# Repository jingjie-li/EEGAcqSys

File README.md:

# EEGAcqSys
A EEG acquisition and online processing system based on ADS1299 and TI DSP

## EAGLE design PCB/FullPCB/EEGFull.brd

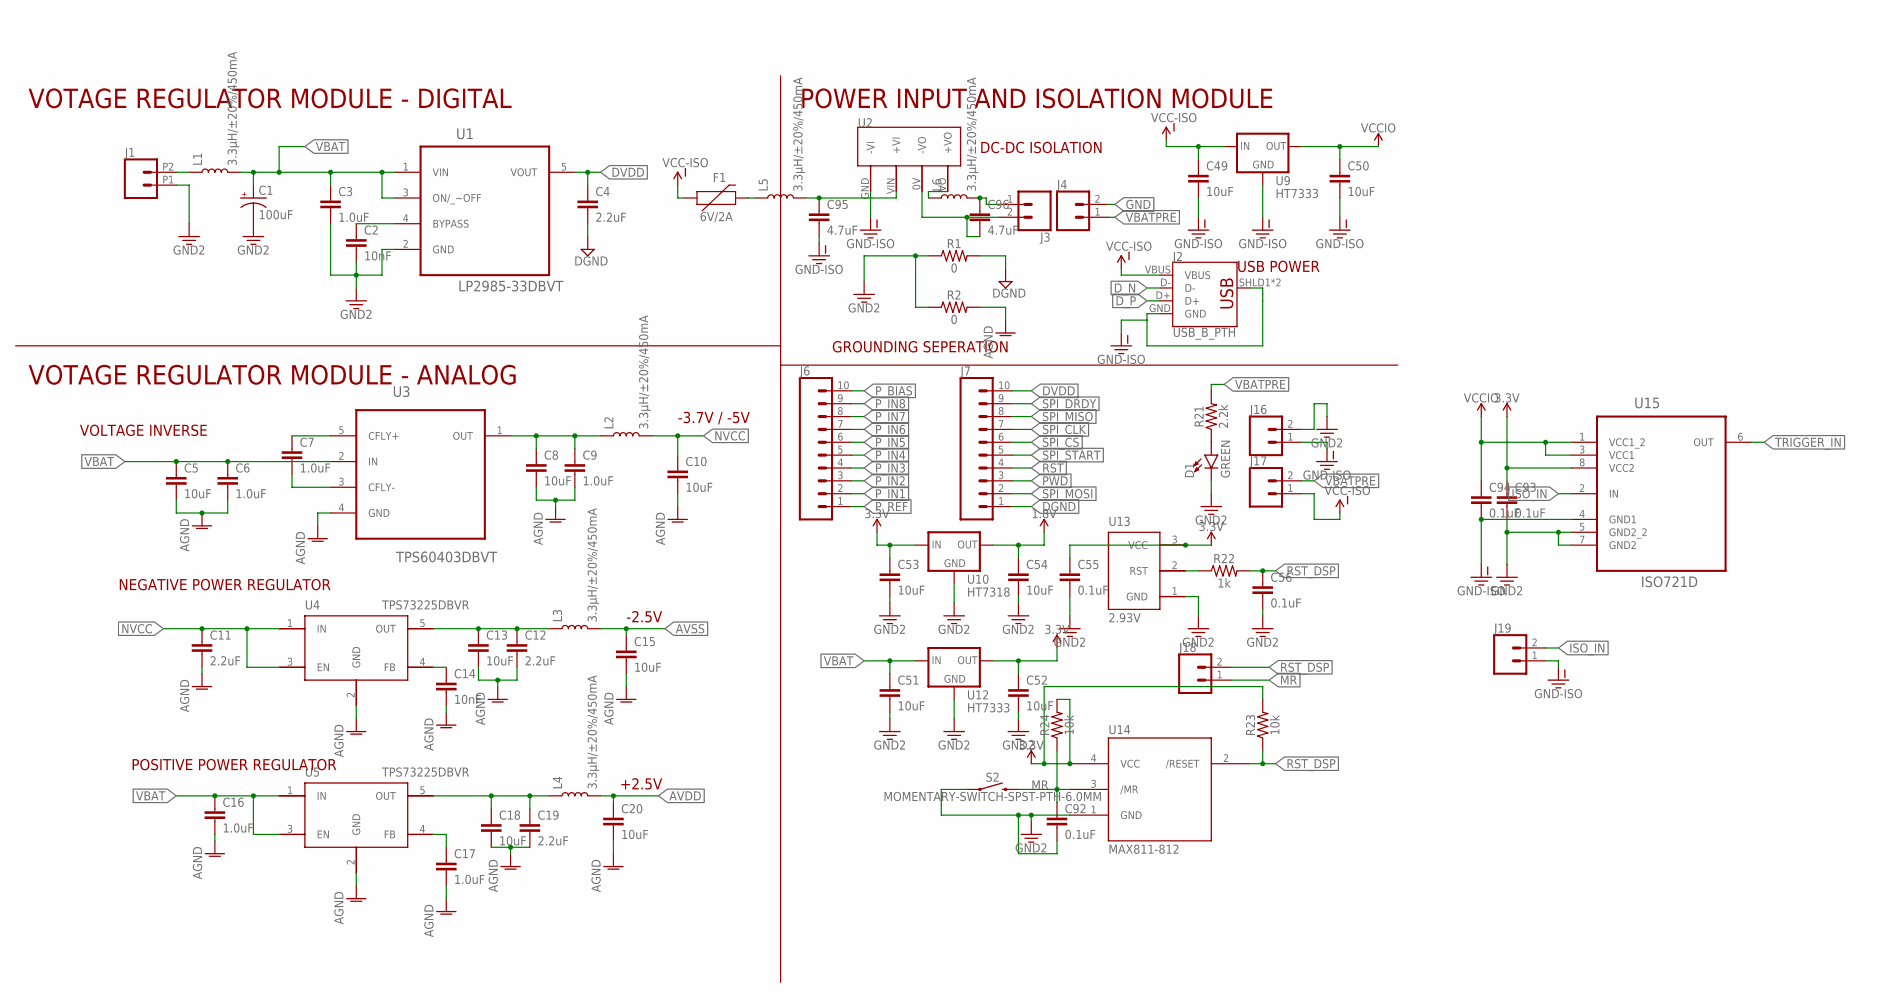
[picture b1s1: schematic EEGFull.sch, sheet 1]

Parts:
C1: 100uF; CPOL-RADIAL-2.5MM-6.5MM
C2, C14: 10nF; 0402
C3, C7, C16, C17: 1.0uF; 0402
C4, C11, C12, C19: 2.2uF; 0603
C5, C8, C10, C13, C15, C18, C20, C49, C50, C51, C52, C53, C54: 10uF; 0603
C6, C9: 1.0uF; 0603
C55, C56, C92, C93, C94: 0.1uF; 0402
C95, C96: 4.7uF; 0603
D1: GREEN; LED-0603
F1: 6V/2A; 1206
J1: CONN_022.54MM_SCREWTERM; 1X02_2.54_SCREWTERM
J2: USB_B_PTH; USB-B-PTH
J3, J4, J16, J17, J18: CONN_02; 1X02
J6, J7: CONN_10"; 1X10
J19: CONN_023.5MM; SCREWTERMINAL-3.5MM-2
L1, L2, L3, L4, L5, L6: 3.3µH/±20%/450mA; 0805
R1, R2: 0; 0402
R21: 2.2k; 0603
R22: 1k; 0402
R23, R24: 10k; 0402
S2: MOMENTARY-SWITCH-SPST-PTH-6.0MM; TACTILE_SWITCH_PTH_6.0MM
U1: LP2985-33DBVT; SOT95P280X145-5N
U2: B0505S-2W-SIP; SIP
U3: TPS60403DBVT; SOT95P280X145-5N
U4, U5: TPS73225DBVR; SOT95P280X145-5N
U9, U12: HT7333; SOT-89
U10: HT7318; SOT-89
U13: 2.93V; SOT23-3
U14: MAX811-812; SOT143
U15: ISO721D; SOIC127P600X175-8N

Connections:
1.8V: C54.1, U10.1 (OUT); also elsewhere on the board
3.3V: C52.1, C53.1, C55.1, C93.1, R23.2, R24.2, U10.3 (IN), U10.4 (IN), U12.1 (OUT), U13.3 (VCC), U14.4 (VCC), U15.8 (VCC2); also elsewhere on the board
AGND: C5.2, C6.2, C8.2, C9.2, C10.2, C11.2, C12.2, C13.2, C14.2, C15.2, C16.2, C17.2, C18.2, C19.2, C20.2, R2.2, U3.4 (GND), U4.2 (GND), U5.2 (GND); also elsewhere on the board
AVDD: C20.1, L4.2; also elsewhere on the board
AVSS: C15.1, L3.2; also elsewhere on the board
BYPASS: C2.1, U1.4 (BYPASS)
DGND: C4.2, J7.1, R1.2; also elsewhere on the board
DVDD: C4.1, J7.10, U1.5 (VOUT); also elsewhere on the board
D_N: J2.D-; also elsewhere on the board
D_P: J2.D+; also elsewhere on the board
GND: C1.2 (-), C2.2, C3.2, C51.2, C52.2, C53.2, C54.2, C55.2, C56.2, C92.2, C93.2, D1.C, J1.P1 (1), J4.2, J16.2, R1.1, R2.1, S2.1, U1.2 (GND), U10.2 (GND), U12.2 (GND), U13.1 (GND), U14.1 (GND), U15.5 (GND2_2), U15.7 (GND2); also elsewhere on the board
GND-ISO: C49.2, C50.2, C94.2, C95.2, J2.GND, J2.SHLD1 (SHIELD), J2.SHLD2 (SHIELD), J16.1, J19.1, U2.GND (-VI), U9.2 (GND), U15.4 (GND1); also elsewhere on the board
ISO_IN: J19.2, U15.2 (IN)
MR: C92.1, J18.1, R24.1, S2.3 (2), U14.3 (/MR)
unnamed: C96.1, J3.1, L6.2
unnamed: C96.2, J3.2, U2.0V (-VO)
unnamed: C7.1, U3.5 (CFLY+)
unnamed: C7.2, U3.3 (CFLY-)
unnamed: C8.1, C9.1, L2.1, U3.1 (OUT)
unnamed: C17.1, U5.4 (FB)
unnamed: C12.1, C13.1, L3.1, U4.5 (OUT)
unnamed: C14.1, U4.4 (FB)
unnamed: C18.1, C19.1, L4.1, U5.5 (OUT)
unnamed: D1.A, R21.1
unnamed: F1.2, L5.1
unnamed: R22.1, U13.2 (RST)
unnamed: C95.1, L5.2, U2.VIN (+VI)
unnamed: L6.1, U2.VO (+VO)
NVCC: C10.1, C11.1, L2.2, U4.1 (IN), U4.3 (EN)
PWD: J7.3; also elsewhere on the board
P_BIAS: J6.10; also elsewhere on the board
P_IN1: J6.2; also elsewhere on the board
P_IN2: J6.3; also elsewhere on the board
P_IN3: J6.4; also elsewhere on the board
P_IN4: J6.5; also elsewhere on the board
P_IN5: J6.6; also elsewhere on the board
P_IN6: J6.7; also elsewhere on the board
P_IN7: J6.8; also elsewhere on the board
P_IN8: J6.9; also elsewhere on the board
P_REF: J6.1; also elsewhere on the board
RST: J7.4; also elsewhere on the board
RST_DSP: C56.1, J18.2, R22.2, R23.1, U14.2 (/RESET); also elsewhere on the board
SPI_CLK: J7.7; also elsewhere on the board
SPI_CS: J7.6; also elsewhere on the board
SPI_DRDY: J7.9; also elsewhere on the board
SPI_MISO: J7.8; also elsewhere on the board
SPI_MOSI: J7.2; also elsewhere on the board
SPI_START: J7.5; also elsewhere on the board
TRIGGER_IN: U15.6 (OUT); also elsewhere on the board
VBAT: C1.1 (+), C3.1, C5.1, C6.1, C16.1, C51.1, L1.2, U1.1 (VIN), U1.3 (ON/_~OFF), U3.2 (IN), U5.1 (IN), U5.3 (EN), U12.3 (IN), U12.4 (IN); also elsewhere on the board
VBATPRE: J1.P2 (2), J4.1, J17.2, L1.1, R21.2
VCC-ISO: C49.1, F1.1, J2.VBUS, J17.1, U9.3 (IN), U9.4 (IN); also elsewhere on the board
VCCIO: C50.1, C94.1, U9.1 (OUT), U15.1 (VCC1_2), U15.3 (VCC1)

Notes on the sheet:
VOTAGE REGULATOR MODULE - DIGITAL
VOTAGE REGULATOR MODULE - ANALOG
POWER INPUT AND ISOLATION MODULE
VOLTAGE INVERSE
NEGATIVE POWER REGULATOR
POSITIVE POWER REGULATOR
-2.5V
+2.5V
-3.7V / -5V
GROUNDING SEPERATION
USB POWER
DC-DC ISOLATION

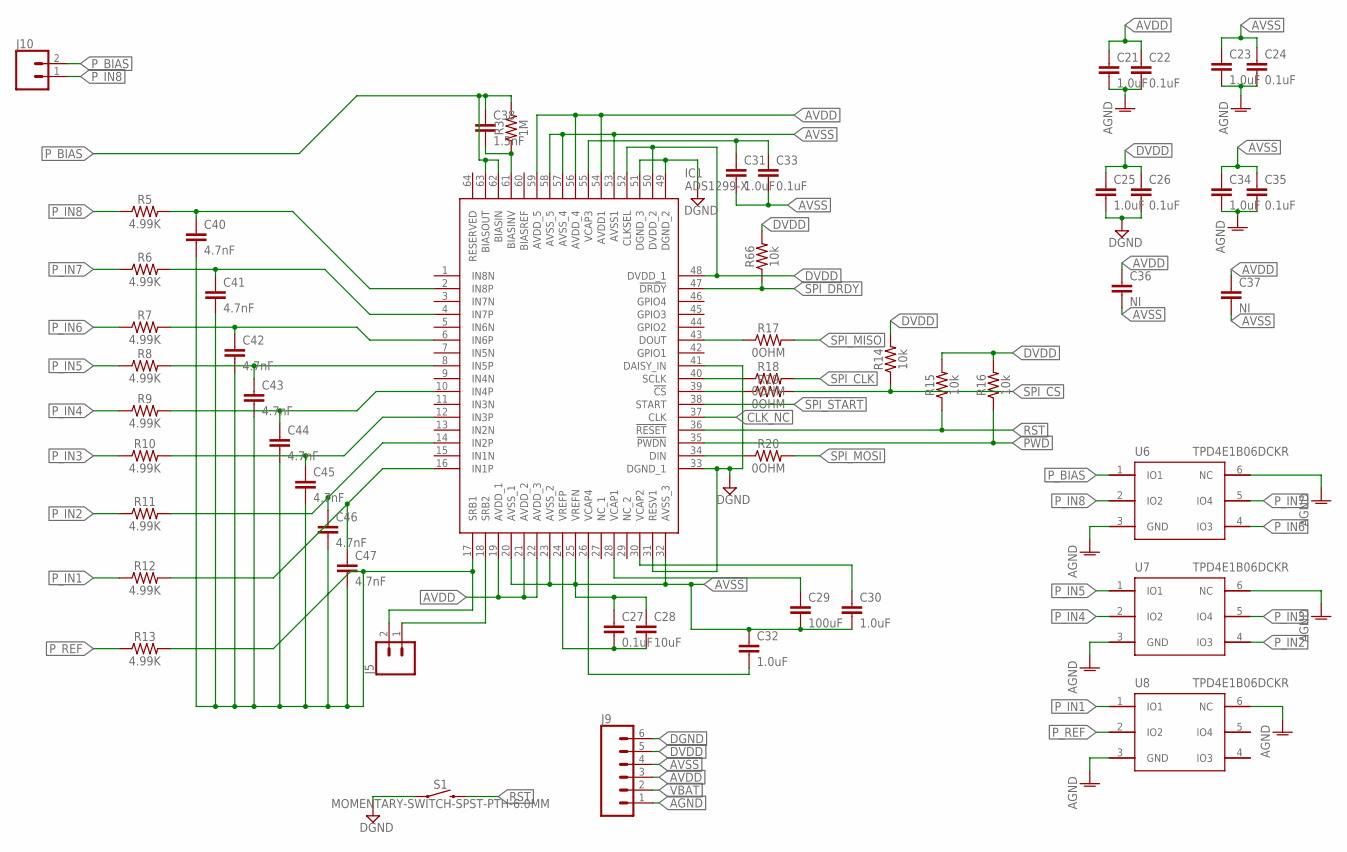
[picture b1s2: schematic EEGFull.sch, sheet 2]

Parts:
C21, C23, C25, C30, C31, C32, C34: 1.0uF; 0402
C22, C24, C26, C27, C33, C35: 0.1uF; 0402
C28: 10uF; 0402
C29: 100uF; 1210
C36, C37: NI; 0402
C38: 1.5nF; 0402
C40, C41, C42, C43, C44, C45, C46, C47: 4.7nF; 0402
IC1: ADS1299-X; QFP50P1200X1200X120-64N
J5, J10: CONN_02; 1X02
J9: CONN_06SILK_FEMALE_PTH; 1X06
R3: 1M; 0402
R5, R6, R7, R8, R9, R10, R11, R12, R13: 4.99K; 0402
R14, R15, R16, R66: 10k; 0402
R17, R18, R19, R20: 0OHM; 0402
S1: MOMENTARY-SWITCH-SPST-PTH-6.0MM; TACTILE_SWITCH_PTH_6.0MM
U6, U7, U8: TPD4E1B06DCKR; SC70-6

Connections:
AGND: C21.2, C22.2, C23.2, C24.2, C34.2, C35.2, J9.1, U6.3 (GND), U6.6 (NC), U7.3 (GND), U7.6 (NC), U8.3 (GND), U8.6 (NC); also elsewhere on the board
AVDD: C21.1, C22.1, C36.1, C37.1, IC1.19 (AVDD_1), IC1.21 (AVDD_2), IC1.22 (AVDD_3), IC1.54 (AVDD1), IC1.56 (AVDD_4), IC1.59 (AVDD_5), J9.3; also elsewhere on the board
AVSS: C23.1, C24.1, C27.1, C28.1, C29.2, C30.2, C31.2, C32.1, C33.2, C34.1, C35.1, C36.2, C37.2, IC1.20 (AVSS_1), IC1.23 (AVSS_2), IC1.25 (VREFN), IC1.32 (AVSS_3), IC1.53 (AVSS1), IC1.57 (AVSS_4), IC1.58 (AVSS_5), J9.4; also elsewhere on the board
CLK_NC: IC1.37 (CLK)
DGND: C25.2, C26.2, IC1.31 (RESV1), IC1.33 (DGND_1), IC1.41 (DAISY_IN), IC1.49 (DGND_2), IC1.51 (DGND_3), J9.6, S1.1; also elsewhere on the board
DVDD: C25.1, C26.1, IC1.48 (DVDD_1), IC1.50 (DVDD_2), IC1.52 (CLKSEL), J9.5, R14.2, R15.2, R16.2, R66.2; also elsewhere on the board
EEG_REF: C40.2, C41.2, C42.2, C43.2, C44.2, C45.2, C46.2, C47.2, IC1.17 (SRB1), J5.2, R13.2
unnamed: C27.2, C28.2, IC1.24 (VREFP)
unnamed: IC1.18 (SRB2), J5.1
unnamed: C38.2, IC1.61 (BIASINV), R3.1
unnamed: C40.1, IC1.2 (IN8P), R5.2
unnamed: C41.1, IC1.4 (IN7P), R6.2
unnamed: C42.1, IC1.6 (IN6P), R7.2
unnamed: C43.1, IC1.8 (IN5P), R8.2
unnamed: C44.1, IC1.10 (IN4P), R9.2
unnamed: C45.1, IC1.12 (IN3P), R10.2
unnamed: C46.1, IC1.14 (IN2P), R11.2
unnamed: C47.1, IC1.16 (IN1P), R12.2
unnamed: IC1.43 (DOUT), R17.1
unnamed: IC1.40 (SCLK), R18.1
unnamed: IC1.39 (!CS), R19.1
unnamed: IC1.34 (DIN), R20.1
PWD: IC1.35 (!PWDN), R16.1; also elsewhere on the board
P_BIAS: C38.1, IC1.62 (BIASIN), IC1.63 (BIASOUT), J10.2, R3.2, U6.1 (IO1); also elsewhere on the board
P_IN1: R12.1, U8.1 (IO1); also elsewhere on the board
P_IN2: R11.1, U7.4 (IO3); also elsewhere on the board
P_IN3: R10.1, U7.5 (IO4); also elsewhere on the board
P_IN4: R9.1, U7.2 (IO2); also elsewhere on the board
P_IN5: R8.1, U7.1 (IO1); also elsewhere on the board
P_IN6: R7.1, U6.4 (IO3); also elsewhere on the board
P_IN7: R6.1, U6.5 (IO4); also elsewhere on the board
P_IN8: J10.1, R5.1, U6.2 (IO2); also elsewhere on the board
P_REF: R13.1, U8.2 (IO2); also elsewhere on the board
RST: IC1.36 (!RESET), R15.1, S1.3 (2); also elsewhere on the board
SPI_CLK: R18.2; also elsewhere on the board
SPI_CS: R14.1, R19.2; also elsewhere on the board
SPI_DRDY: IC1.47 (!DRDY), R66.1; also elsewhere on the board
SPI_MISO: R17.2; also elsewhere on the board
SPI_MOSI: R20.2; also elsewhere on the board
SPI_START: IC1.38 (START); also elsewhere on the board
VBAT: J9.2; also elsewhere on the board
VCAP1: C29.1, IC1.28 (VCAP1)
VCAP2: C30.1, IC1.30 (VCAP2)
VCAP3: C31.1, C33.1, IC1.55 (VCAP3)
VCAP4: C32.2, IC1.26 (VCAP4)

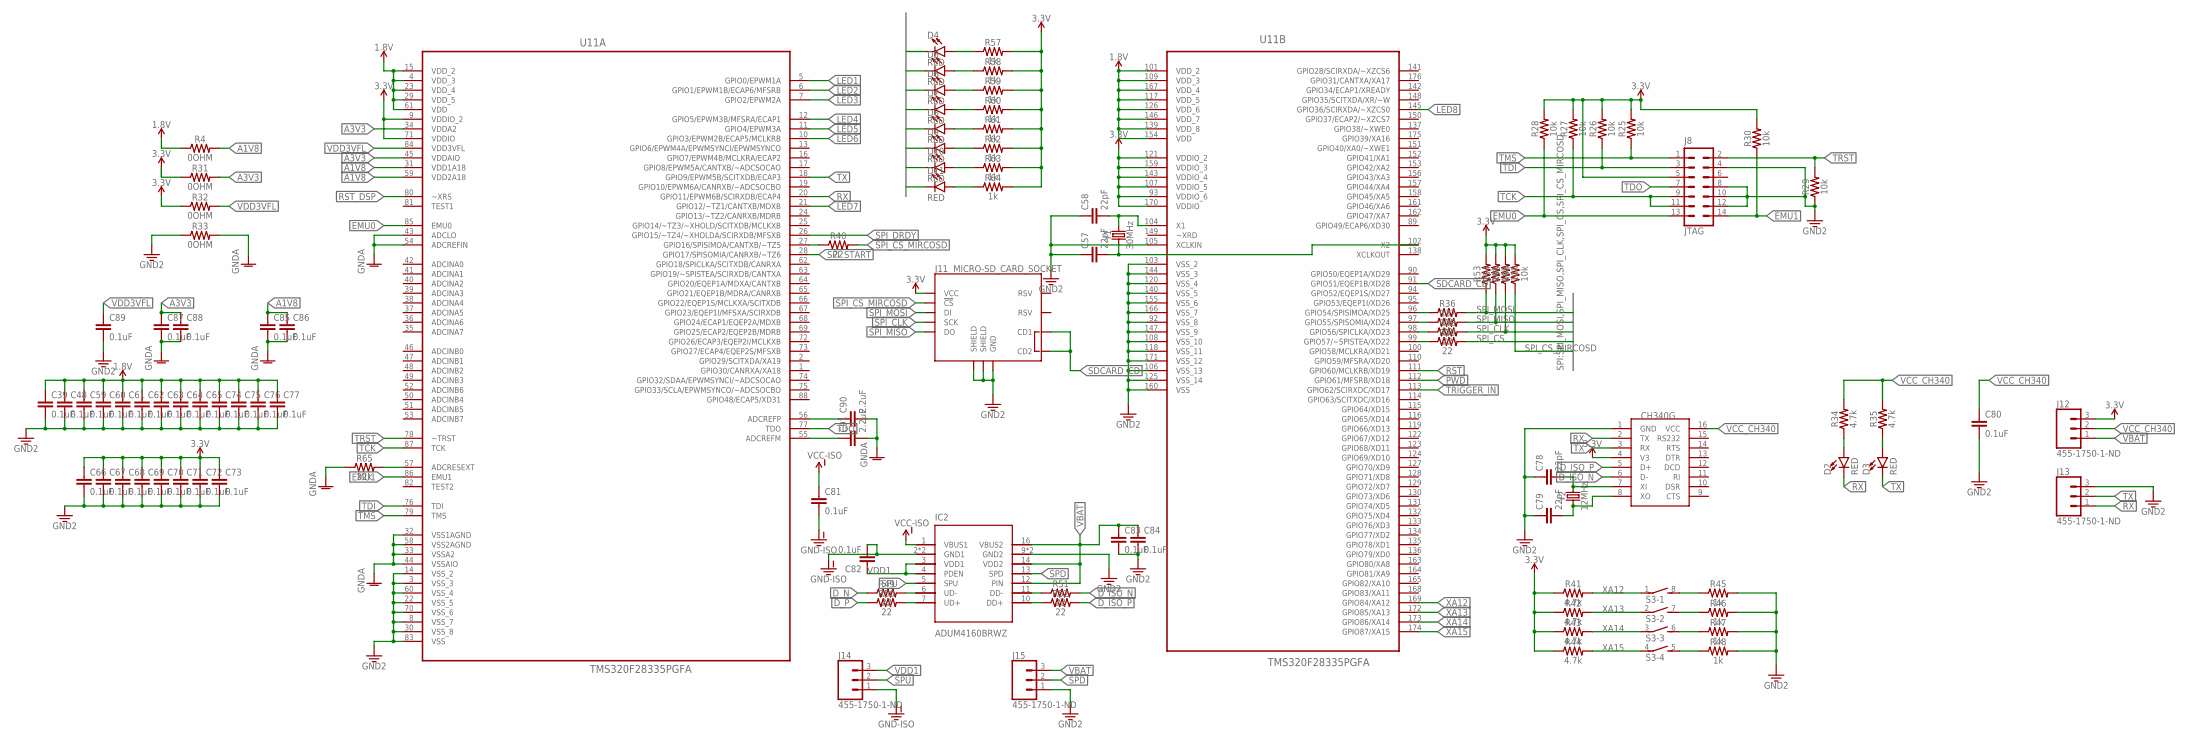
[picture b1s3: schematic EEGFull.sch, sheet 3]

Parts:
C39, C48, C59, C60, C61, C62, C63, C64, C65, C66, C67, C68, C69, C70, C71, C72, C73, C74, C75, C76, C77, C80, C81, C82, C83, C84, C85, C86, C87, C88, C89: 0.1uF; 0402
C57, C58, C78, C79: 22pF; 0402
C90, C91: 2.2uF; 0402
D2, D3, D4, D5, D6, D7, D8, D9, D10, D11: RED; LED-0603
IC2: ADUM4160BRWZ; SOIC127P1032X265-16N
J8: JTAG; 2X7
J11: MICRO-SD_CARD_SOCKET; MICRO-SD-SOCKET
J12, J13, J14, J15: 455-1750-1-ND; 1X03
R4, R31, R32, R33: 0OHM; 0402
R25, R26, R27, R28, R29, R30, R53, R54, R55, R56: 10k; 0402
R34, R35, R41, R42, R43, R44: 4.7k; 0402
R36, R37, R38, R39, R40, R49, R50, R51, R52: 22; 0402
R45, R46, R47, R48, R57, R58, R59, R60, R61, R62, R63, R64: 1k; 0402
R65: 22k; 0402
S3: DIP04S
U11: TMS320F28335PGFA; QFP50P2600X2600X160-176N
U$3: CH340G; SOIC16
Y1: 30MHz; CRYSTAL-SMD-3.2X2.5MM
Y2: 12MHz; CRYSTAL-SMD-3.2X2.5MM

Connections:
1.8V: C39.1, C48.1, C59.1, C60.1, C61.1, C62.1, C63.1, C64.1, C65.1, C74.1, C75.1, C76.1, C77.1, R4.1, U11.4 (VDD_3), U11.15 (VDD_2), U11.23 (VDD_4), U11.29 (VDD_5), U11.61 (VDD), U11.101 (VDD_2), U11.109 (VDD_3), U11.117 (VDD_5), U11.126 (VDD_6), U11.139 (VDD_8), U11.146 (VDD_7), U11.154 (VDD), U11.167 (VDD_4); also elsewhere on the board
3.3V: C66.1, C67.1, C68.1, C69.1, C70.1, C71.1, C72.1, C73.1, J8.5, J11.VCC, J12.3, R25.2, R26.2, R27.2, R28.2, R30.2, R31.1, R32.1, R41.1, R42.1, R43.1, R44.1, R53.2, R54.2, R55.2, R56.2, R57.2, R58.2, R59.2, R60.2, R61.2, R62.2, R63.2, R64.2, U11.9 (VDDIO_2), U11.71 (VDDIO), U11.93 (VDDIO_6), U11.107 (VDDIO_5), U11.121 (VDDIO_2), U11.143 (VDDIO_4), U11.159 (VDDIO_3), U11.170 (VDDIO), U$3.4 (V3); also elsewhere on the board
A1V8: C85.1, C86.1, R4.2, U11.31 (VDD1A18), U11.59 (VDD2A18)
A3V3: C87.1, C88.1, R31.2, U11.34 (VDDA2), U11.45 (VDDAIO)
D_ISO_N: R51.2, U$3.6 (D-)
D_ISO_P: R52.2, U$3.5 (D+)
D_ISO_PRE_N: IC2.11 (DD-), R51.1
D_ISO_PRE_P: IC2.10 (DD+), R52.1
D_N: R49.1; also elsewhere on the board
D_P: R50.1; also elsewhere on the board
EMU0: J8.13, R28.1, U11.85 (EMU0)
EMU1: J8.14, R30.1, U11.86 (EMU1)
GND: C39.2, C48.2, C57.1, C58.1, C59.2, C60.2, C61.2, C62.2, C63.2, C64.2, C65.2, C66.2, C67.2, C68.2, C69.2, C70.2, C71.2, C72.2, C73.2, C74.2, C75.2, C76.2, C77.2, C78.1, C79.1, C80.2, C83.2, C84.2, C89.2, IC2.9 (GND2), IC2.15 (GND2), J8.4, J8.8, J8.10, J8.12, J11.GND, J11.GND1 (SHIELD), J11.GND3 (SHIELD), J13.3, J15.1, R29.1, R33.1, R45.2, R46.2, R47.2, R48.2, U11.3 (VSS_3), U11.8 (VSS_7), U11.14 (VSS_2), U11.22 (VSS_5), U11.30 (VSS_8), U11.60 (VSS_4), U11.70 (VSS_6), U11.83 (VSS), U11.92 (VSS_8), U11.103 (VSS_2), U11.105 (XCLKIN), U11.106 (VSS_13), U11.108 (VSS_10), U11.118 (VSS_11), U11.120 (VSS_4), U11.125 (VSS_14), U11.140 (VSS_5), U11.144 (VSS_3), U11.147 (VSS_9), U11.155 (VSS_6), U11.160 (VSS), U11.166 (VSS_7), U11.171 (VSS_12), U$3.1 (GND); also elsewhere on the board
GND-ISO: C81.2, C82.2, IC2.2 (GND1), IC2.8 (GND1), J14.1; also elsewhere on the board
GNDA: C85.2, C86.2, C87.2, C88.2, C90.2, C91.2, R33.2, R65.1, U11.32 (VSS1AGND), U11.33 (VSSA2), U11.43 (ADCLO), U11.44 (VSSAIO), U11.54 (ADCREFIN), U11.58 (VSS2AGND)
LED1: D4.C, U11.5 (GPIO0/EPWM1A)
LED2: D5.C, U11.6 (GPIO1/EPWM1B/ECAP6/MFSRB)
LED3: D6.C, U11.7 (GPIO2/EPWM2A)
LED4: D7.C, U11.12 (GPIO5/EPWM3B/MFSRA/ECAP1)
LED5: D8.C, U11.11 (GPIO4/EPWM3A)
LED6: D9.C, U11.10 (GPIO3/EPWM2B/ECAP5/MCLKRB)
LED7: D10.C, U11.21 (GPIO12/~TZ1/CANTXB/MDXB)
LED8: D11.C, U11.145 (GPIO36/SCIRXDA/~XZCS0)
unnamed: C78.2, U$3.7 (XI), Y2.3 (2)
unnamed: C79.2, U$3.8 (XO), Y2.1
unnamed: C58.2, U11.104 (X1), Y1.3 (2)
unnamed: C57.2, U11.102 (X2), Y1.1
unnamed: D11.A, R64.1
unnamed: D2.A, R34.1
unnamed: D3.A, R35.1
unnamed: R36.1, U11.96 (GPIO54/SPISIMOA/XD25)
unnamed: IC2.6 (UD-), R49.2
unnamed: R37.1, U11.97 (GPIO55/SPISOMIA/XD24)
unnamed: R38.1, U11.98 (GPIO56/SPICLKA/XD23)
unnamed: R39.1, U11.99 (GPIO57/~SPISTEA/XD22)
unnamed: R40.1, U11.27 (GPIO16/SPISIMOA/CANTXB/~TZ5)
unnamed: IC2.7 (UD+), R50.2
unnamed: D10.A, R63.1
unnamed: D9.A, R62.1
unnamed: D8.A, R61.1
unnamed: D7.A, R60.1
unnamed: D6.A, R59.1
unnamed: D5.A, R58.1
unnamed: D4.A, R57.1
unnamed: C90.1, U11.56 (ADCREFP)
unnamed: C91.1, U11.55 (ADCREFM)
unnamed: R65.2, U11.57 (ADCRESEXT)
unnamed: R48.1, S3.5 (2)
unnamed: R47.1, S3.6 (2)
unnamed: R46.1, S3.7 (2)
unnamed: R45.1, S3.8 (2)
PWD: U11.112 (GPIO61/MFSRB/XD18); also elsewhere on the board
RST: U11.111 (GPIO60/MCLKRB/XD19); also elsewhere on the board
RST_DSP: U11.80 (~XRS); also elsewhere on the board
RX: D2.C, J13.1, U11.20 (GPIO11/EPWM6B/SCIRXDB/ECAP4), U$3.2 (TX)
SDCARD_CD: J11.CD1, J11.CD2, U11.91 (GPIO51/EQEP1B/XD28)
SPD: IC2.13 (SPD), J15.2
SPI_CLK: J11.SCLK (SCK), R38.2, R55.1; also elsewhere on the board
SPI_CS: R39.2; also elsewhere on the board
SPI_CS_MIRCOSD: J11.CS (!CS), R40.2, R56.1
SPI_DRDY: U11.26 (GPIO15/~TZ4/~XHOLDA/SCIRXDB/MFSXB); also elsewhere on the board
SPI_MISO: J11.DO, R37.2, R54.1; also elsewhere on the board
SPI_MOSI: J11.DI, R36.2, R53.1; also elsewhere on the board
SPI_START: U11.28 (GPIO17/SPISOMIA/CANRXB/~TZ6); also elsewhere on the board
SPU: IC2.5 (SPU), J14.2
TCK: J8.9, J8.11, R27.1, U11.87 (TCK)
TDI: J8.3, R26.1, U11.76 (TDI)
TDO: J8.7, U11.77 (TDO)
TMS: J8.1, R25.1, U11.79 (TMS)
TRIGGER_IN: U11.113 (GPIO62/SCIRXDC/XD17); also elsewhere on the board
TRST: J8.2, R29.2, U11.78 (~TRST)
TX: D3.C, J13.2, U11.18 (GPIO9/EPWM5B/SCITXDB/ECAP3), U$3.3 (RX)
VBAT: C83.1, C84.1, IC2.12 (PIN), IC2.14 (VDD2), IC2.16 (VBUS2), J12.1, J15.3; also elsewhere on the board
VCC-ISO: C81.1, IC2.1 (VBUS1); also elsewhere on the board
VCC_CH340: C80.1, J12.2, R34.2, R35.2, U$3.16 (VCC)
VDD1: C82.1, IC2.3 (VDD1), IC2.4 (PDEN), J14.3
VDD3VFL: C89.1, R32.2, U11.84 (VDD3VFL)
XA12: R41.2, S3.1, U11.169 (GPIO84/XA12)
XA13: R42.2, S3.2 (1), U11.172 (GPIO85/XA13)
XA14: R43.2, S3.3 (1), U11.173 (GPIO86/XA14)
XA15: R44.2, S3.4 (1), U11.174 (GPIO87/XA15)

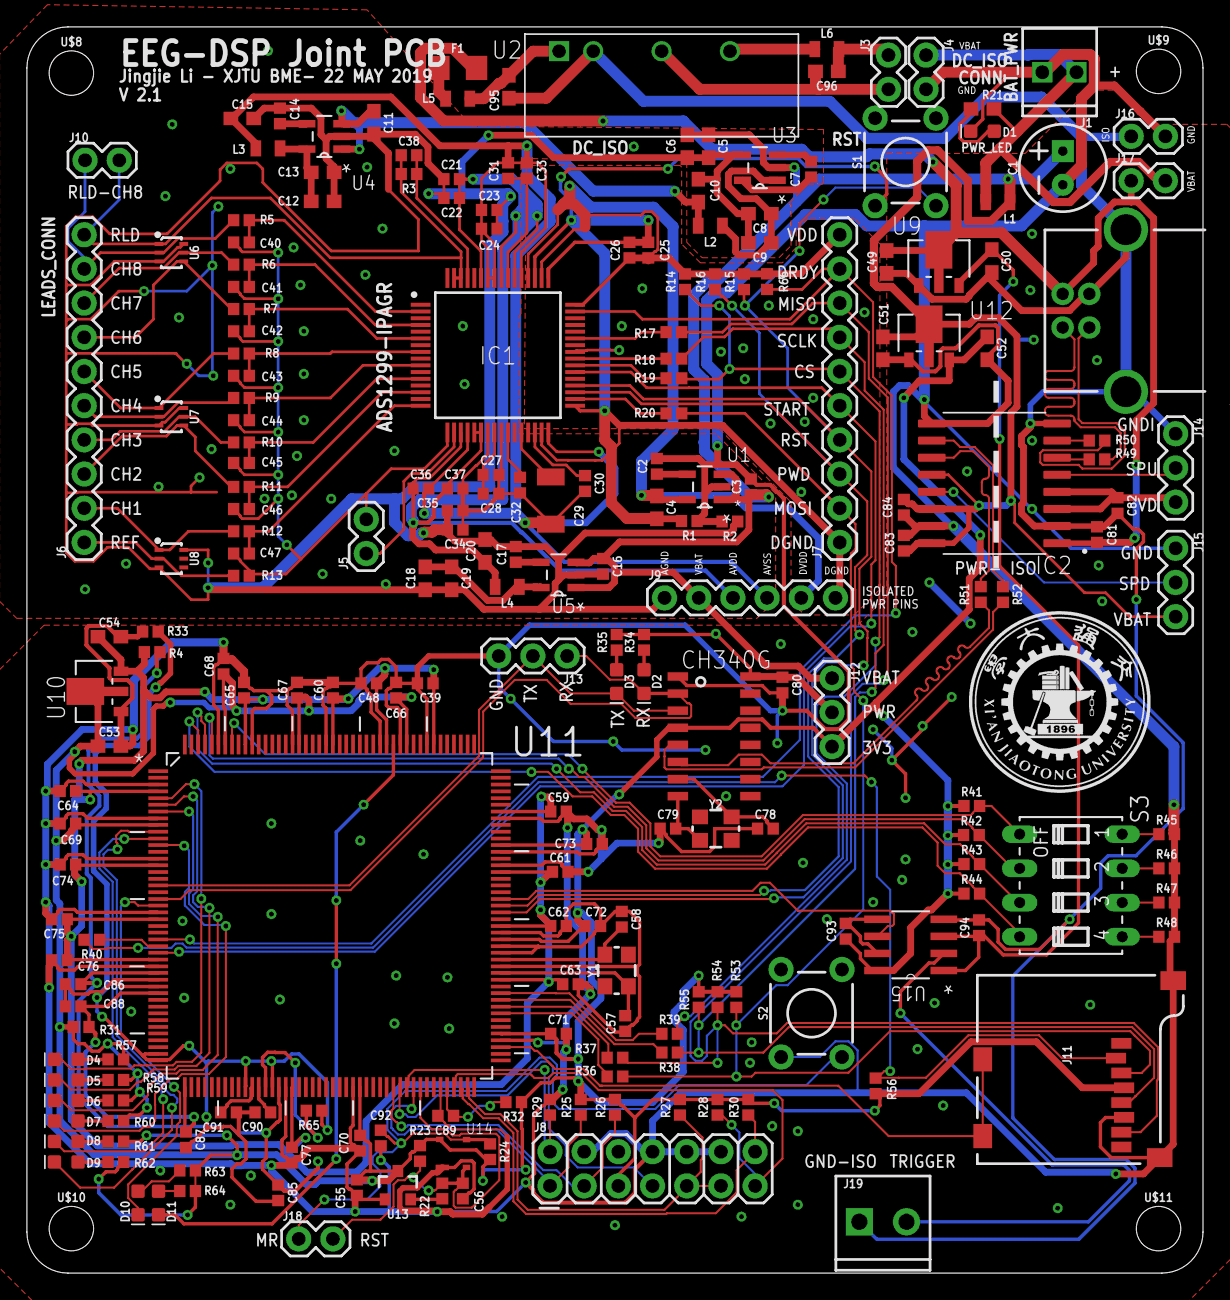
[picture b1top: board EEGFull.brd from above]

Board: 2 copper layers, 87.4 x 92.6 mm, 227 parts (0 on the bottom side), 136 nets.

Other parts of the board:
U$7: XJTULOGO
U$8, U$9, U$10, U$11: STAND-OFF

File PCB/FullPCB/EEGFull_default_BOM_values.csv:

Qty,Value,Device,Parts,Package,Description,DESCRIPTION,HEIGHT,MANUFACTURER_NAME,MANUFACTURER_PART_NUMBER,MF,MOUSER_PART_NUMBER,MOUSER_PRICE-STOCK,MPN,OC_FARNELL,OC_NEWARK,PACKAGE,PROD_ID,RS_PART_NUMBER,RS_PRICE-STOCK,SF_ID,SF_SKU,SUPPLIER,VALUE
42,0.1uF,0.1UF-0402-16V-10%,"C22, C24, C26, C27, C33, C35, C39, C48, C55, C56, C59, C60, C61, C62, C63, C64, C65, C66, C67, C68, C69, C70, C71, C72, C73, C74, C75, C76, C77, C80, C81, C82, C83, C84, C85, C86, C87, C88, C89, C92, C93, C94",402,0.1åµF ceramic capacitors,,,,,,,,,,,,CAP-12416,,,,,,0.1uF
2,NI,0.1UF-0402-16V-10%,"C36, C37",402,0.1åµF ceramic capacitors,,,,,,,,,,,,CAP-12416,,,,,,0.1uF
8,0OHM,0OHM,"R4, R17, R18, R19, R20, R31, R32, R33",402,0ë© resistor,,,,,,,,,,,,,,,,,,
11,1.0uF,1.0UF-0402-16V-10%,"C3, C7, C16, C17, C21, C23, C25, C30, C31, C32, C34",402,1åµF ceramic capacitors,,,,,,,,,,,,CAP-12417,,,,,,1.0uF
2,1.0uF,1.0UF-0603-16V-10%,"C6, C9",603,1åµF ceramic capacitors,,,,,,,,,,,,CAP-00868,,,,,,1.0uF
1,1.5nF,1.5NF-0402,C38,402,,,,,,,,,,,,,,,,,,,1.5nF
1,100uF,100UF-1210-20%-10V,C29,1210,,,,,,,,,,,,,,,,,,,100uF
1,100uF,100UF-POLAR-RADIAL-2.5MM-25V-20%,C1,CPOL-RADIAL-2.5MM-6.5MM,100åµF polarized capacitors,,,,,,,,,,,,CAP-08439,,,,,,100uF
16,10k,10KOHM-0402-1/10W-1%,"R14, R15, R16, R23, R24, R25, R26, R27, R28, R29, R30, R53, R54, R55, R56, R66",402,10kë© resistor,,,,,,,,,,,,,,,,,,10k
2,10nF,10NF-0402-50V-10%,"C2, C14",402,"0.01uF/10nF/10,000pF ceramic capacitors",,,,,,,,,,,,,,,,,,10nF
1,10uF,10UF-0402-6.3V-20%,C28,402,10.0åµF ceramic capacitors,,,,,,,,,,,,,,,,,,10uF
13,10uF,10UF-0603-6.3V-20%,"C5, C8, C10, C13, C15, C18, C20, C49, C50, C51, C52, C53, C54",603,10.0åµF ceramic capacitors,,,,,,,,,,,,CAP-11015,,,,,,10uF
13,1k,1KOHM-0402-1%,"R22, R45, R46, R47, R48, R57, R58, R59, R60, R61, R62, R63, R64",402,1kë© resistor,,,,,,,,,,,,,,,,,,1k
1,1M,1MOHM-0402-1/4W-5%,R3,402,1Më© resistor,,,,,,,,,,,,C26083,,,,,,1M
1,2.2k,2.2KOHM-0603-1/10W-1%,R21,603,2.2kë© resistor,,,,,,,,,,,,RES-08272,,,,,,2.2k
2,2.2uF,2.2UF-0402-10V-20%,"C90, C91",402,2.2åµF ceramic capacitors,,,,,,,,,,,,,,,,,,2.2uF
4,2.2uF,2.2UF-0603-10V-20%,"C4, C11, C12, C19",603,2.2åµF ceramic capacitors,,,,,,,,,,,,CAP-07888,,,,,,2.2uF
1,22k,22KOHM0402-1/10W-1%,R65,402,22kë© resistor,,,,,,,,,,,,,,,,,,22k
9,22,22OHM-0402-1/10W-1%,"R36, R37, R38, R39, R40, R49, R50, R51, R52",402,22ë© resistor,,,,,,,,,,,,RES-12427,,,,,,22
4,22pF,22PF-0402-50V-5%,"C57, C58, C78, C79",402,22pF ceramic capacitors,,,,,,,,,,,,,,,,,,22pF
6,4.7k,4.7KOHM-0402-1/10W-1%,"R34, R35, R41, R42, R43, R44",402,4.7kë© resistor,,,,,,,,,,,,,,,,,,4.7k
8,4.7nF,4.7NF-0402,"C40, C41, C42, C43, C44, C45, C46, C47",402,,,,,,,,,,,,,,,,,,,4.7nF
2,4.7uF,4.7UF0603,"C95, C96",603,4.7åµF ceramic capacitors,,,,,,,,,,,,CAP-08280,,,,,,4.7uF
9,4.99K,4.99KOHM-0402,"R5, R6, R7, R8, R9, R10, R11, R12, R13",402,,,,,,,,,,,,,,,,,,,4.99K
2,0,560OHM_0402_1%,"R1, R2",402,,,,,,,,,,,,,RES-13766,,,,,,560
1,ADS1299-X,ADS1299-X,IC1,QFP50P1200X1200X120-64N,ADS1299-x 24-Bit  Analog-to-Digital Converters (ADCs),ADS1299-x 24-Bit  Analog-to-Digital Converters (ADCs),1.2mm,Texas Instruments,ADS1299-X,,,,,,,,,,,,,,
1,ADUM4160BRWZ,ADUM4160BRWZ,IC2,SOIC127P1032X265-16N,,,,,,,,,,,,,,,,,,,
1,,B0505S-2W-SIP,U2,SIP,,,,,,,,,,,,,,,,,,,
1,CH340G,CH340G,U$3,SOIC16,,,,,,,,,,,,,,,,,,,
7,,CONN_02,"J3, J4, J5, J10, J16, J17, J18",1X02,Multi connection point. Often used as Generic Header-pin footprint for 0.1 inch spaced/style header connections,,,,,,,,,,,,,,,,,,
1,,CONN_022.54MM_SCREWTERM,J1,1X02_2.54_SCREWTERM,Multi connection point. Often used as Generic Header-pin footprint for 0.1 inch spaced/style header connections,,,,,,,,,,,,,,,,,,
1,,CONN_023.5MM,J19,SCREWTERMINAL-3.5MM-2,Multi connection point. Often used as Generic Header-pin footprint for 0.1 inch spaced/style header connections,,,,,,,,,,,,CONN-08399,,,,,,
4,455-1750-1-ND,CONN_03,"J12, J13, J14, J15",1X03,Multi connection point. Often used as Generic Header-pin footprint for 0.1 inch spaced/style header connections,,,,,,,,,,,,XXX-00000,,,,,,455-1750-1-ND
1,,CONN_06SILK_FEMALE_PTH,J9,1X06,Multi connection point. Often used as Generic Header-pin footprint for 0.1 inch spaced/style header connections,,,,,,,,,,,,CONN-08437,,,,,,
1,JTAG,CONN_07X2,J8,2X7,,,,,,,,,,,,,,,,,,,
2,,"CONN_10"",J6"," J7""",1X10,Multi connection point. Often used as Generic Header-pin footprint for 0.1 inch spaced/style header connections,,,,,,,,,,,,CONN-11563,,,,,,
1,12MHz,CRYSTALSMD-3.2X2.5,Y2,CRYSTAL-SMD-3.2X2.5MM,Crystals (Generic),,,,,,,,,,,,,,,,,,
1,30MHz,CRYSTALSMD-3.2X2.5,Y1,CRYSTAL-SMD-3.2X2.5MM,Crystals (Generic),,,,,,,,,,,,,,,,,,
1,,DIP04S,S3,DIP04S,DIL/CODE SWITCH,,,,,,,,,unknown,unknown,,,,,,,,
1,HT7318,HT7318,U10,SOT-89,,,,,,,,,,,,,,,,,,,
2,HT7333,HT7333,"U9, U12",SOT-89,,,,,,,,,,,,,,,,,,,
1,2.93V,IMP809SEUR-T,U13,SOT23-3,,,,,,,,,,,,,,,,,,,2.93V
6,3.3åµH/å±20%/450mA,INDUCTOR-0805-3.3UH,"L1, L2, L3, L4, L5, L6",805,Inductors,,,,,,,,,,,,NDUC-13076,,,,,,3.3åµH/å±20%/450mA
1,ISO721D,ISO721D,U15,SOIC127P600X175-8N,3.3-V / 5-V HIGH-SPEED DIGITAL ISOLATORS,,,,,,,,ISO721D,-,74K5333,SOIC-8,,,,,,Texas Instruments,
1,GREEN,LED-GREEN0603,D1,LED-0603,Green SMD LED,,,,,,,,,,,,DIO-00821,,,,,,GREEN
10,RED,LED-RED0603,"D2, D3, D4, D5, D6, D7, D8, D9, D10, D11",LED-0603,Red SMD LED,,,,,,,,,,,,DIO-00819,,,,,,RED
1,LP2985-33DBVT,LP2985-33DBVT,U1,SOT95P280X145-5N,150-mA LOW-NOISE LOW-DROPOUT REGULATOR WITH SHUTDOWN,,,,,,,,LP2985-33DBVT,-,43J9347,SOT-23-5,,,,,,Texas Instruments,
1,MAX811-812,MAX811-812,U14,SOT143,MAX811/MAX812 4-Pin åµP Voltage Monitors with Manual Reset Input,,,,,,,,,,,,,,,,,,
1,MICRO-SD_CARD_SOCKET,MICRO-SD_CARD_SOCKET,J11,MICRO-SD-SOCKET,microSD Socket for Transflash,,,,,,,,,,,,CONN-07820,,,PRT-00127,,,
2,MOMENTARY-SWITCH-SPST-PTH-6.0MM,MOMENTARY-SWITCH-SPST-PTH-6.0MM,"S1, S2",TACTILE_SWITCH_PTH_6.0MM,Momentary Switch (Pushbutton) - SPST,,,,,,,,,,,, SWCH-08441,,,,COM-00097,,
1,6V/2A,PPTC_HALF-AMP,F1,1206,Resettable Fuse PPTC,,,,,,,,,,,,RES-08585,,,,,,6V/0.5A
1,TMS320F28335PGFA,TMS320F28335PGFA,U11,QFP50P2600X2600X160-176N,Digital Signal Controllers,,,,,,,,TMS320F28335PGFA,1901870,11N7235,QFP-176,,,,,,TEXAS INSTRUMENTS,
3,TPD4E1B06DCKR,TPD4E1B06DCKR,"U6, U7, U8",SC70-6,,,,,,,,,,,,,,,,,,,
1,TPS60403DBVT,TPS60403DBVT,U3,SOT95P280X145-5N,Unregulated 60 mA Charge pump voltage Inverter,,,,,,,,TPS60403DBVT,8457786,77C0632,SOT-23-5,,,,,,Texas Instruments,
2,TPS73225DBVR,TPS73225DBVR,"U4, U5",SOT95P280X145-5N,,,,,,,,,,,,,,,,,,,
1,USB_B_PTH,USB_B_PTH,J2,USB-B-PTH,USB Type B Connector,,,,,,,,,,,,CONN-08278,,,PRT-00139,,,

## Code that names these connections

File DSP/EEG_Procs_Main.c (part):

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#include "DSP2833x_Device.h"     // DSP2833x Headerfile Include File
#include "DSP2833x_Examples.h"   // DSP2833x Examples Include File
/********************************ºê¶¨ÒåÊýÂë¹ÜÎ»Ñ¡ IO ½Ó¿Ú*******************************************/
#define  SET_BIT4	GpioDataRegs.GPASET.bit.GPIO16	 = 1 		//CS = 1					
#define  RST_BIT4	GpioDataRegs.GPACLEAR.bit.GPIO16 = 1		//CS = 0
#define  SET_BIT3   GpioDataRegs.GPASET.bit.GPIO17	 = 1		//START  = 1
#define  RST_BIT3	GpioDataRegs.GPACLEAR.bit.GPIO17 = 1		//START  = 0
#define  SET_BIT2   GpioDataRegs.GPBSET.bit.GPIO60	 = 1		//RST IO62
#define  RST_BIT2	GpioDataRegs.GPBCLEAR.bit.GPIO60 = 1		//ÓëÍâÉè°å 8_LEDS ¶Ë×ÓµÄ IO54 ¶ÔÓ¦
#define  SET_BIT1   GpioDataRegs.GPBSET.bit.GPIO61	 = 1		//PWD IO61
#define  RST_BIT1	GpioDataRegs.GPBCLEAR.bit.GPIO61 = 1		//ÓëÍâÉè°å 8_LEDS ¶Ë×ÓµÄ IO55 ¶ÔÓ¦
#define LED1_OFF		GpioDataRegs.GPASET.bit.GPIO0 = 1							//LED D10 on
#define LED1_ON			GpioDataRegs.GPACLEAR.bit.GPIO0 = 1						//LED D10 off
#define LED2_OFF		GpioDataRegs.GPASET.bit.GPIO1 = 1							//LED D11 on
#define LED2_ON			GpioDataRegs.GPACLEAR.bit.GPIO1 = 1						//LED D11 off
#define LED3_OFF		GpioDataRegs.GPASET.bit.GPIO2 = 1							//LED D12 on
#define LED3_ON			GpioDataRegs.GPACLEAR.bit.GPIO2 = 1						//LED D12 off
#define LED4_OFF		GpioDataRegs.GPASET.bit.GPIO3 = 1							//LED D13 on
#define LED4_ON			GpioDataRegs.GPACLEAR.bit.GPIO3 = 1						//LED D13 off
/*****************************************************************************************************/


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    EALLOW;
   
	
	GpioCtrlRegs.GPAPUD.bit.GPIO16= 0;   					// Enable pullup on GPIO11
    GpioDataRegs.GPASET.bit.GPIO16 = 1;   					// Load output latch
    GpioCtrlRegs.GPAMUX2.bit.GPIO16 = 0;  					// GPIO16 = GPIO
    GpioCtrlRegs.GPADIR.bit.GPIO16 = 1;   					// GPIO16 = output

	GpioCtrlRegs.GPAPUD.bit.GPIO17= 0;   					// Enable pullup on GPIO11
    GpioDataRegs.GPASET.bit.GPIO17 = 1;   					// Load output latch
    GpioCtrlRegs.GPAMUX2.bit.GPIO17 = 0;  					// GPIO16 = GPIO
    GpioCtrlRegs.GPADIR.bit.GPIO17 = 1;   					// GPIO16 = output
    
	GpioCtrlRegs.GPBPUD.bit.GPIO60 = 0;   					// Enable pullup on GPIO11
    GpioDataRegs.GPBSET.bit.GPIO60 = 1;   					// Load output latch
    GpioCtrlRegs.GPBMUX2.bit.GPIO60 = 0;  					// GPIO17 = GPIO
    GpioCtrlRegs.GPBDIR.bit.GPIO60 = 1;   					// GPIO17 = output
    
	GpioCtrlRegs.GPBPUD.bit.GPIO61 = 0;   					// Enable pullup on GPIO11
    GpioDataRegs.GPBSET.bit.GPIO61 = 1;   					// Load output latch
    GpioCtrlRegs.GPBMUX2.bit.GPIO61 = 0;  					// GPIO19 = GPIO
    GpioCtrlRegs.GPBDIR.bit.GPIO61 = 1;   					// GPIO19 = output
    
    
    GpioCtrlRegs.GPAMUX1.bit.GPIO15 = 0;   //congifure input
    GpioCtrlRegs.GPADIR.bit.GPIO15 = 0;   
    
     //LED D10 
	GpioCtrlRegs.GPAPUD.bit.GPIO0 = 0;   									// Enable pullup on GPIO11
    GpioDataRegs.GPASET.bit.GPIO0 = 1;   									// Load output latch
    GpioCtrlRegs.GPAMUX1.bit.GPIO0 = 0;  									// GPIO11 = GPIO
    GpioCtrlRegs.GPADIR.bit.GPIO0 = 1;   									// GPIO11 = output    
	//LED D11
	GpioCtrlRegs.GPAPUD.bit.GPIO1 = 0;   									// Enable pullup on GPIO11
    GpioDataRegs.GPASET.bit.GPIO1 = 1;   									// Load output latch
    GpioCtrlRegs.GPAMUX1.bit.GPIO1 = 0;  									// GPIO11 = GPIO
    GpioCtrlRegs.GPADIR.bit.GPIO1 = 1;   									// GPIO11 = output    
	//LED D12
	GpioCtrlRegs.GPAPUD.bit.GPIO2 = 0;   									// Enable pullup on GPIO11
    GpioDataRegs.GPASET.bit.GPIO2 = 1;   									// Load output latch
    GpioCtrlRegs.GPAMUX1.bit.GPIO2 = 0;  									// GPIO11 = GPIO
    GpioCtrlRegs.GPADIR.bit.GPIO2 = 1;   									// GPIO11 = output   
	//LED D13    
    GpioCtrlRegs.GPAPUD.bit.GPIO3 = 0;   									// Enable pullup on GPIO11
    GpioDataRegs.GPASET.bit.GPIO3 = 1;   									// Load output latch
    GpioCtrlRegs.GPAMUX1.bit.GPIO3 = 0;  									// GPIO11 = GPIO
    GpioCtrlRegs.GPADIR.bit.GPIO3 = 1;   									// GPIO11 = output  

    EDIS;  
    
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   	Spi_Rcv_Data=SpiaRegs.SPIRXBUF;	
   	for(ii=0;ii<600;ii++)
   	{
   	  	while (GpioDataRegs.GPADAT.bit.GPIO15==1) {} //DRDY is in high
   	  	ads1299_RDATAC(Data_Rcv);
   	  	//ads1299_ConvRcvData(Data_Rcv,&EEGCH1,&EEGCH2,&EEGCH3,&EEGCH4,&EEGCH5,&EEGCH6,&EEGCH7,&EEGCH8,&STAT_Data);
   	  	ads1299_SendUARTRaw(Data_Rcv);
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   	
   	for(;;)
   	{
   	  	while (GpioDataRegs.GPADAT.bit.GPIO15==1) {} //DRDY is in high
   	  	ads1299_RDATAC(Data_Rcv);
   	  	//ads1299_ConvRcvData(Data_Rcv,&EEGCH1,&EEGCH2,&EEGCH3,&EEGCH4,&EEGCH5,&EEGCH6,&EEGCH7,&EEGCH8,&STAT_Data);
   	  	ads1299_SendUARTRaw(Data_Rcv);
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   	
   	for(;;)
   	{
   		//while (GpioDataRegs.GPADAT.bit.GPIO15==0) {} //DRDY is in high
   	  	while (GpioDataRegs.GPADAT.bit.GPIO15==1) {} //DRDY is in high
   	  	ads1299_RDATAC(Data_Rcv);
   	  	//ads1299_ConvRcvData(Data_Rcv,&EEGCH1,&EEGCH2,&EEGCH3,&EEGCH4,&EEGCH5,&EEGCH6,&EEGCH7,&EEGCH8,&STAT_Data);
   	  	ads1299_SendUARTRaw(Data_Rcv);
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
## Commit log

2019-03-19 code
2019-03-20 PCB power parts
2019-03-20 ads stuff init
2019-03-21 STUFF
2019-03-22 partly complete the ADS part
2019-03-23 SPI_ISO
2019-03-23 PCB wiring complete
2019-03-24 text adjusting & add power pins and less
2019-03-25 front only PCB complete!
2019-03-25 ADD gerber, BOM and SMT pos files
2019-04-02 ads1299 spi code
2019-04-03 improve SPI reading
2019-04-19 update guy
2019-04-19 Revert "update guy"
    This reverts commit 80b4e61ff4da07388e47631cd085fe8bc7981739.
2019-04-19 Revert "Revert "update guy""
    This reverts commit 8ccc27f17946e5c1777cf8efbfd3746bfba457f5.
2019-04-21 Main BOM
2019-04-21 cost comp chart
2019-04-24 fix data receiving bug
2019-04-25 update baseline compute function
2019-04-25 change to float & add offset calb
2019-04-25 fixed static baseline compute code
2019-04-27 upload the GUI
2019-04-27 fix data cannot received bug
2019-04-27 update file
2019-04-28 update the test_mode
2019-04-28 fix the bug that can not receive the data
2019-04-28 add gitignore
2019-04-29 Add filter
2019-04-29 ignore distort
2019-04-29 add the FFT window animation but need to be refreshed
2019-04-29 high pass
2019-04-29 fixed the realtime running problem
2019-04-29 just to pull
2019-04-30 加入了 按x 键退出程序并关停硬件的功能。
2019-05-04 add the band power plot
2019-05-04 update stuff
2019-05-06 Make the bandPower Right
2019-05-06 add full pub
2019-05-06 add funtion to on-off button
2019-05-06 update main pcb
2019-05-06 Add stop all button
2019-05-07 add high pass filter
2019-05-07 update pcb & update dsp main code
2019-05-10 full pcb nearly complete
2019-05-12 GND copper cover
2019-05-22 update DSP main program
2019-05-22 update EEG ADS PCB
2019-05-22 update Full PCB
2019-05-23 start doing thesis

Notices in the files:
parts and their libraries:
SparkFun-Connectors: Licensing: Creative Commons ShareAlike 4.0 International - https://creativecommons.org/licenses/by-sa/4.0
m-pad-2.1: License : GNU General Public License version 2 (see bottom)
